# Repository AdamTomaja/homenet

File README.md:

# Home-Net
What is Home-Net? Home-Net is a project which will make Your Home Smart :) 
With Home-Net You can script Your devices in JavaScript and Control them from WEB.

# Screenshots
## Home-Net: Main Page

## Home-Net: Control Panel

# Configuring system and running UMU
## Network Configuration
MQTT Broker has to be configured with static IP.
To do this, please reconfigure Your /etc/dhcpcd.conf file as follows:

```bash
interface wlan0
static ip_address 192.168.0.10/24
static routers=192.168.0.1
static domain_name_servers=127.0.0.1 8.8.8.8 8.8.4.4
```

## TimeZone Configuration
Please remember to set Your timezone on Linux where UMU is installed. 
This is important because You can use time in Javascript flows. 
For example hour is used to determine if turn lights on when motion is detected.

```bash
sudo dpkg-reconfigure tzdata
```

## Start MQTT broker
Please a compatible MQTT broker for the homenet infrastructure. 
I suggest to use Mosquitto. 
You can run install it and run using following command: 

```bash
service mosquitto start
```

## Install Grafana and Influx DB
* Install InfluxDB
```bash
apt-get install influxdb
```

* Check the status of grafana service
```bash
service influxd status
```
You can also open web interface of influxdb: **http://host:8083**

* Install and start the Grafana
```bash
apt-get install grafana
service grafana-server start
```

* Check the status of Grafana **http://host:3000**

## Run UMU server
Execute following command in **homenet-server** directory
```bash
maven spring-boot:run
```

# MQTT Topics
This is description of MQTT topics used by HomeNet UCU and UMU. 

| Topic name          | Description                                                                    | Message class        |
|---------------------|--------------------------------------------------------------------------------|----------------------|
| /ucu/gpio/configure | configure gpio direction, input output pullup                                  | ConfigureGpioMessage |
| /ucu/gpio/set       | set value for gpio on ucu                                                      | SetGpioValueMessage  |
| /umu/gpio/set       | gpio value changed on ucu                                                      | SetGpioValueMessage  |
| /ucu/hello          | request to all ucus to send message to umu with instance names                 | HelloMessage         |
| /umu/hello          | all ucus can introduce themselfs to umu                                        | HelloMessage         |
| /umu/error          | ucu sends to this topic information about errors                               | ErrorMessage         |
| /umu/ping           | ucus sends ping message as answer for ping message from umu                    | PingMessage          |
| /ucu/ping           | umu send ping request to all ucus                                              | PingMessage          |

# UCU Connector
| Signal    | Wire Color    | Connector Pin     |
|-----------|---------------|-------------------|
| 5V        | Red           | 1                 |
| 3.3V      | White         | 2                 |
| IO        | Blue          | 3                 |
| GND       | Black         | 4                 |

# LCU - Light Control Unit - Specification
* One 230V Relay output
* Integrated 5V Power Supply
* External Reset Button - in case of BUGs in software
* External MicroUSB port - for programming
* Fixed to wall like normal light switch - using metal frame from common light switch
* External BLS 2x2 Ports for additional sensors and devices `(GND, 5V, 3.3V, GPIO)`
* Fallback to direct power to light

### NodeMCU Pin Capabilities
| IO Index  | Esp8266 pin   | OUTPUT    | INPUT             | Function          |
|-----------|-------------  |-----------|-------------------|-------------------|
| 0         | Gpio16        | X         | --- (USER Led)    | Notification LED  |
| 1         | Gpio5         | X         | X                 | IO0               |
| 2         | Gpio4         | X         | X                 | IO1               |
| 3         | Gpio0         | X         | X (Flash Button)  | IO2               |   
| 4         | Gpio2         | X         | X                 | IO3               |
| 5         | Gpio14        | X         | X                 | IO4               | 
| 6         | Gpio12        | X         | X                 | IO5               |
| 7         | Gpio13        | X         | X                 | IO6               |
| 8         | Gpio15        | X         | X/2 BOOT,NOPULLUP | Relay             |
| 11 - SD2  | Gpio9         | X         | X                 | Button A          |
| 12 - SD3  | Gpio10        | X         | X                 | Button B          |
| A0        | ADC0          | ---       | ---               | IO8               |

# UMU Configuration
```json
{
  "mqtt": {
    "host": "rpi-umu",
    "port": 1883
  },
  "instances": [
    {
      "id": "ucu-389469",
      "name": "Daily Room",
      "description": "Room I live in",
      "gpios": [
        {
          "name": "Button",
          "mode": "INPUT",
          "isPullup": true,
          "pin": 3,
          "invert": true
        },
        {
          "name": "Led",
          "mode": "OUTPUT",
          "isPullup": false,
          "pin": 4,
          "initialValue": 1,
          "invert": true
        }
      ]
    }
  ]
}
```

## HomeLets
Homelets are small Javascript application which are used to add some logic to Your home behavior. 
The api is very is simple and similar to Arduino. You have setup method and loop. 
It`s possible to add listeners for given control unit and gpio. Also it``s possible last known value of gpio or set new value of output. 

This is example homelet, responsible for turning  on the light when motion is detected or turning off when no  motion detected for 15 minutes.

```javascript
/** Consts **/
var adamsRoom = "Adam Room";
var lightRelay = "Light Relay";
var motionSensor = "Motion Sensor";

var LIGHTS_OFF_TIMEOUT = 15 * 60;

/* Global Variables */
var lastMovementTime = 0;

/* Methods */
function getTimestamp() {
    return new Date().getTime();
}

function getHours() {
    return new Date().getHours();
}

setup = function() {
    this.addListener(adamsRoom, motionSensor, function(value) {
        if(value) {
            var hour = getHours();
            if(hour >= 18 && hour <= 22) {
                this.setValue(adamsRoom, lightRelay, 0);
            }
        }
    });
}

loop = function() {

    var motionSensorValue = this.getValue(adamsRoom, motionSensor);
    var currentTimestamp = getTimestamp();

    if(motionSensorValue) {
        lastMovementTime = currentTimestamp;
    }

    var secondsElapsed = (currentTimestamp - lastMovementTime) / 1000;
    if(secondsElapsed > LIGHTS_OFF_TIMEOUT) {
        this.setValue(adamsRoom, lightRelay, 1);
    }
}
```

# UCU Configuration
Every UCU has embedded configuration server service. 

It exposes WIFI Access Point with Http server. AP will be automatically disabled after 60 seconds after boot time.
Name of AP is the same as chipid (instanceId). 

To configure UCU You should connect with UCU with WiFi and send following http request:
## UCU Configuration Http Request
* host: `192.168.4.1`
* port: `80`
* method: `POST`
* path: `/`
* headers:
    * **ssid** - wifi SSID
    * **password** - wifi PASSWORD
    * **mqtt-host** - MQTT Broker Host
    * **mqtt-port** - MQTT Broker Port

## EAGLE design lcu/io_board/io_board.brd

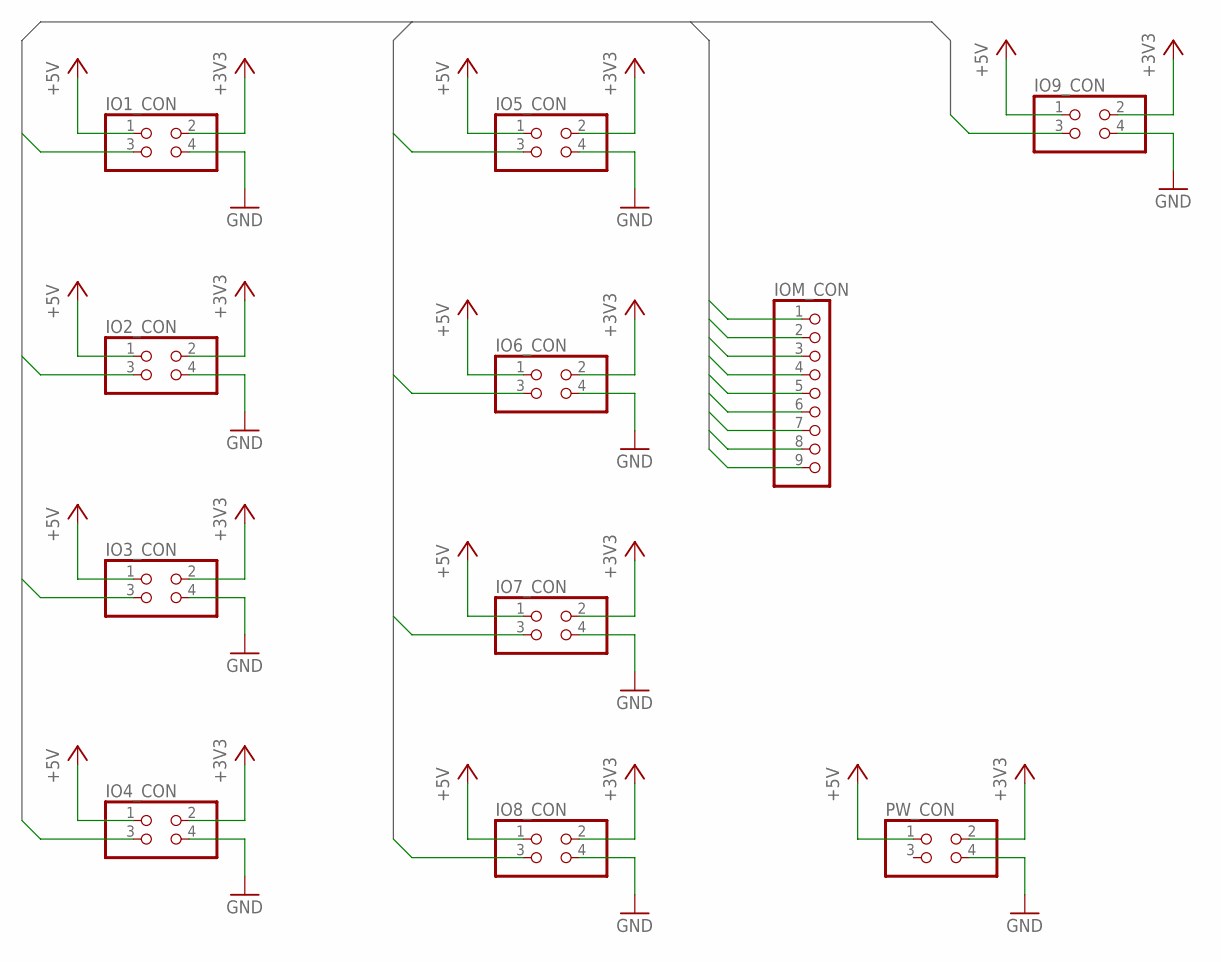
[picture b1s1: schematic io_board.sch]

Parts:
IO1_CON, IO2_CON, IO3_CON, IO4_CON, IO5_CON, IO6_CON, IO7_CON, IO8_CON, IO9_CON: PINHD-2X2; 2X02
IOM_CON: PINHD-1X9; 1X09
PW_CON: PINHD-2X2; 2X02

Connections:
+3V3: IO1_CON.2, IO2_CON.2, IO3_CON.2, IO4_CON.2, IO5_CON.2, IO6_CON.2, IO7_CON.2, IO8_CON.2, IO9_CON.2, PW_CON.2
+5V: IO1_CON.1, IO2_CON.1, IO3_CON.1, IO4_CON.1, IO5_CON.1, IO6_CON.1, IO7_CON.1, IO8_CON.1, IO9_CON.1, PW_CON.1
GND: IO1_CON.4, IO2_CON.4, IO3_CON.4, IO4_CON.4, IO5_CON.4, IO6_CON.4, IO7_CON.4, IO8_CON.4, IO9_CON.4, PW_CON.4
IO0: IO1_CON.3, IOM_CON.1
IO1: IO2_CON.3, IOM_CON.2
IO2: IO3_CON.3, IOM_CON.3
IO3: IO4_CON.3, IOM_CON.4
IO4: IO5_CON.3, IOM_CON.5
IO5: IO6_CON.3, IOM_CON.6
IO6: IO7_CON.3, IOM_CON.7
IO7: IO8_CON.3, IOM_CON.8
IO8: IO9_CON.3, IOM_CON.9

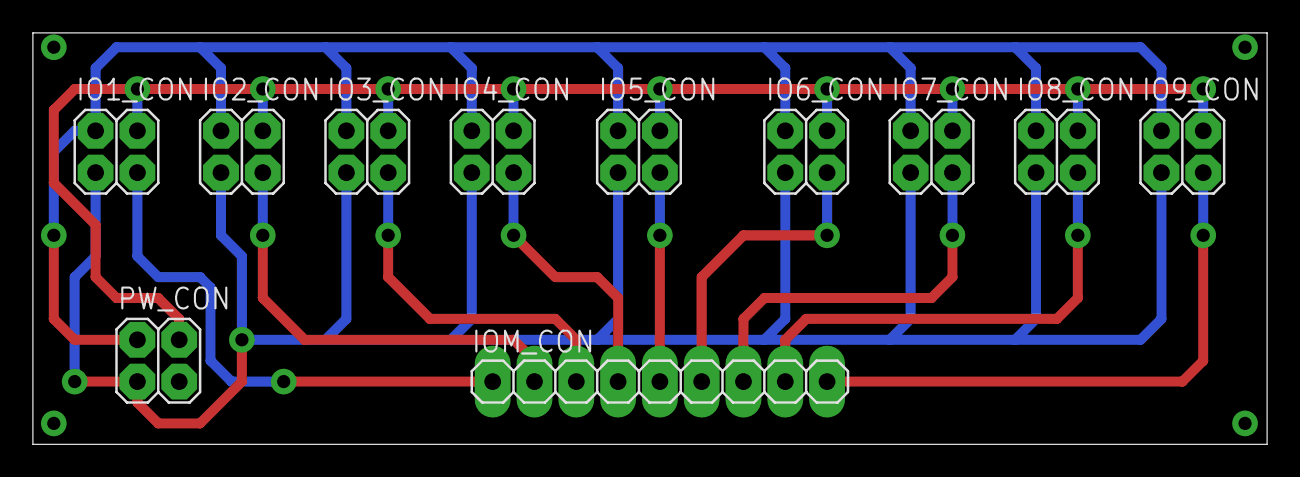
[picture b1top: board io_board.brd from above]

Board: 2 copper layers, 75.0 x 25.0 mm, 11 parts (0 on the bottom side), 12 nets.

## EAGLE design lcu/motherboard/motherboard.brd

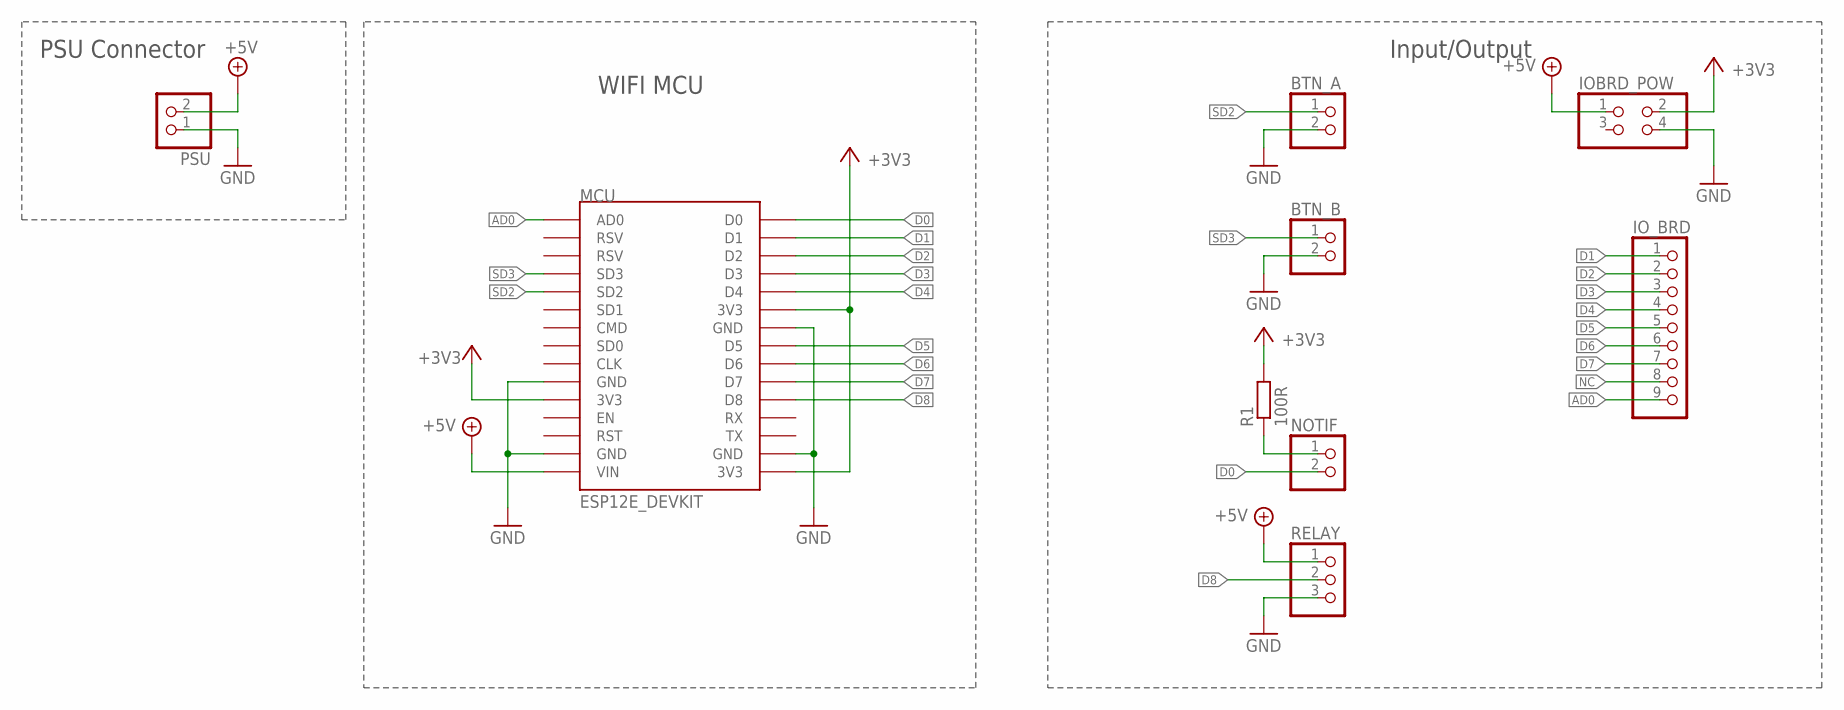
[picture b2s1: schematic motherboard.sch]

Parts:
BTN_A: PINHD-1X2; 1X02
BTN_B: PINHD-1X2; 1X02
IOBRD_POW: PINHD-2X2; 2X02
IO_BRD: PINHD-1X9; 1X09
MCU: ESP12E_DEVKIT
NOTIF: PINHD-1X2; 1X02
PSU: PINHD-1X2; 1X02
R1: 100R; 0204/7
RELAY: PINHD-1X3; 1X03

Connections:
+3V3: IOBRD_POW.2, MCU.3V3@0 (3V3), MCU.3V3@1 (3V3), MCU.3V3@2 (3V3), R1.2
+5V: IOBRD_POW.1, MCU.VIN, PSU.2, RELAY.1
AD0: IO_BRD.9, MCU.AD0
D0: MCU.D0, NOTIF.2
D1: IO_BRD.1, MCU.D1
D2: IO_BRD.2, MCU.D2
D3: IO_BRD.3, MCU.D3
D4: IO_BRD.4, MCU.D4
D5: IO_BRD.5, MCU.D5
D6: IO_BRD.6, MCU.D6
D7: IO_BRD.7, MCU.D7
D8: MCU.D8, RELAY.2
GND: BTN_A.2, BTN_B.2, IOBRD_POW.4, MCU.GND@0 (GND), MCU.GND@1 (GND), MCU.GND@2 (GND), MCU.GND@3 (GND), PSU.1, RELAY.3
unnamed: NOTIF.1, R1.1
NC: IO_BRD.8
SD2: BTN_A.1, MCU.SD2
SD3: BTN_B.1, MCU.SD3

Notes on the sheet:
PSU Connector
Input/Output
WIFI MCU

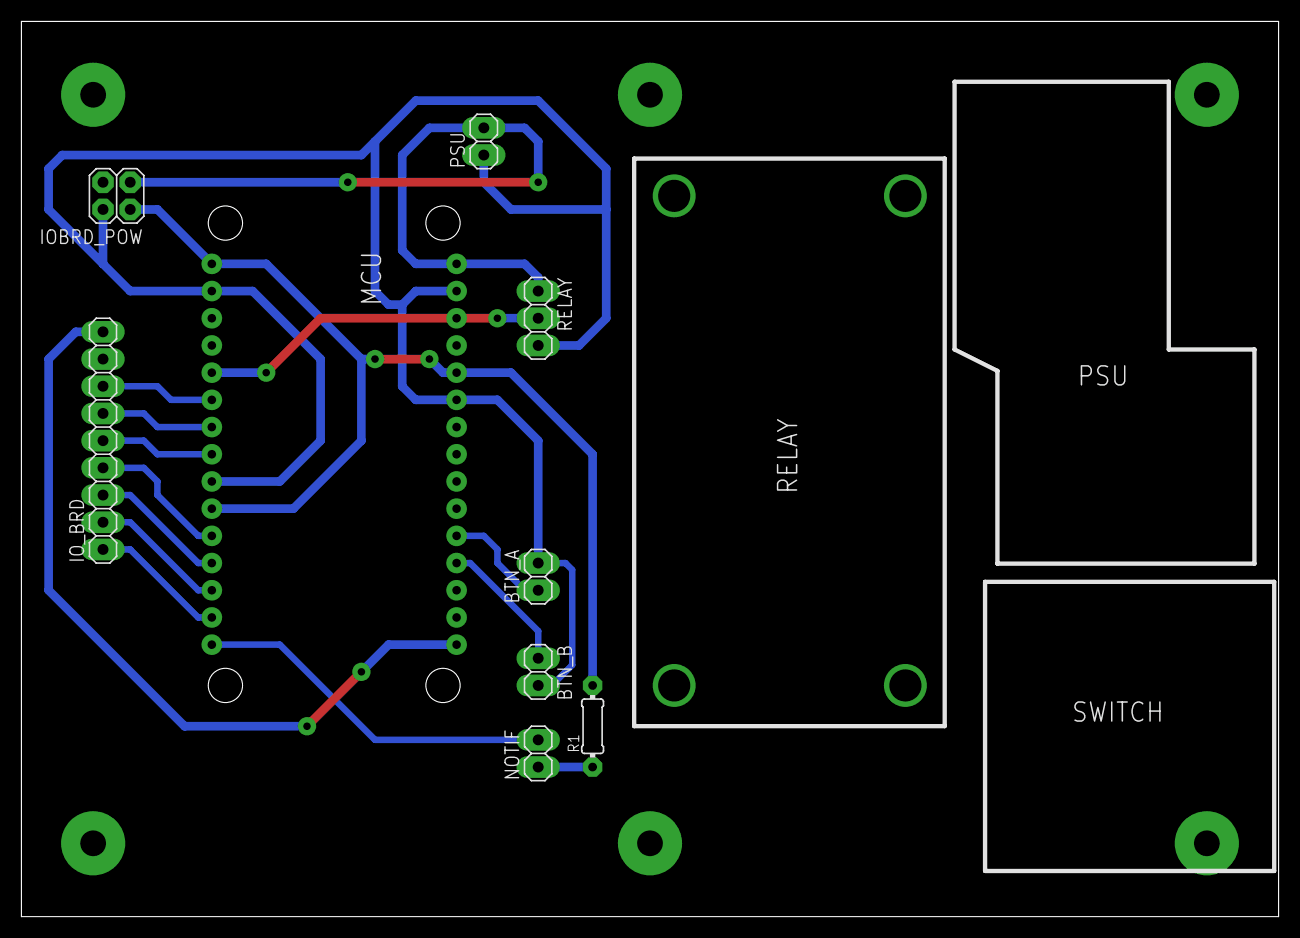
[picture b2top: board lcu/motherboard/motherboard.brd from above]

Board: 2 copper layers, 117.4 x 83.6 mm, 9 parts (0 on the bottom side), 16 nets.

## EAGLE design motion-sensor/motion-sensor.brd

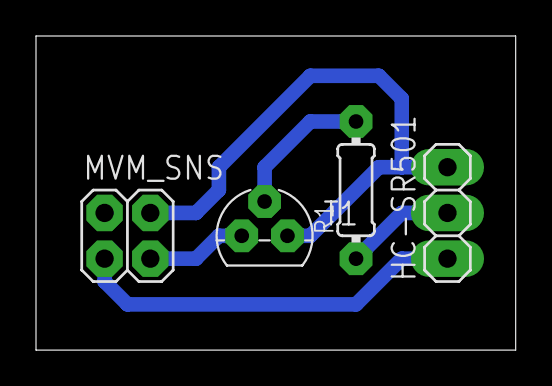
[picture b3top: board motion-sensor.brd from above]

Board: 2 copper layers, 26.6 x 17.4 mm, 4 parts (0 on the bottom side), 5 nets.

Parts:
HC-SR501: 1X03
MVM_SNS: 2X02
R1: 0204/7
T1: BC547; TO92

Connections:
+5V: HC-SR501.1, MVM_SNS.1
GND: HC-SR501.3, MVM_SNS.4, T1.1
unnamed: R1.2, T1.2
unnamed: HC-SR501.2, R1.1
OUTPUT: MVM_SNS.3, T1.3

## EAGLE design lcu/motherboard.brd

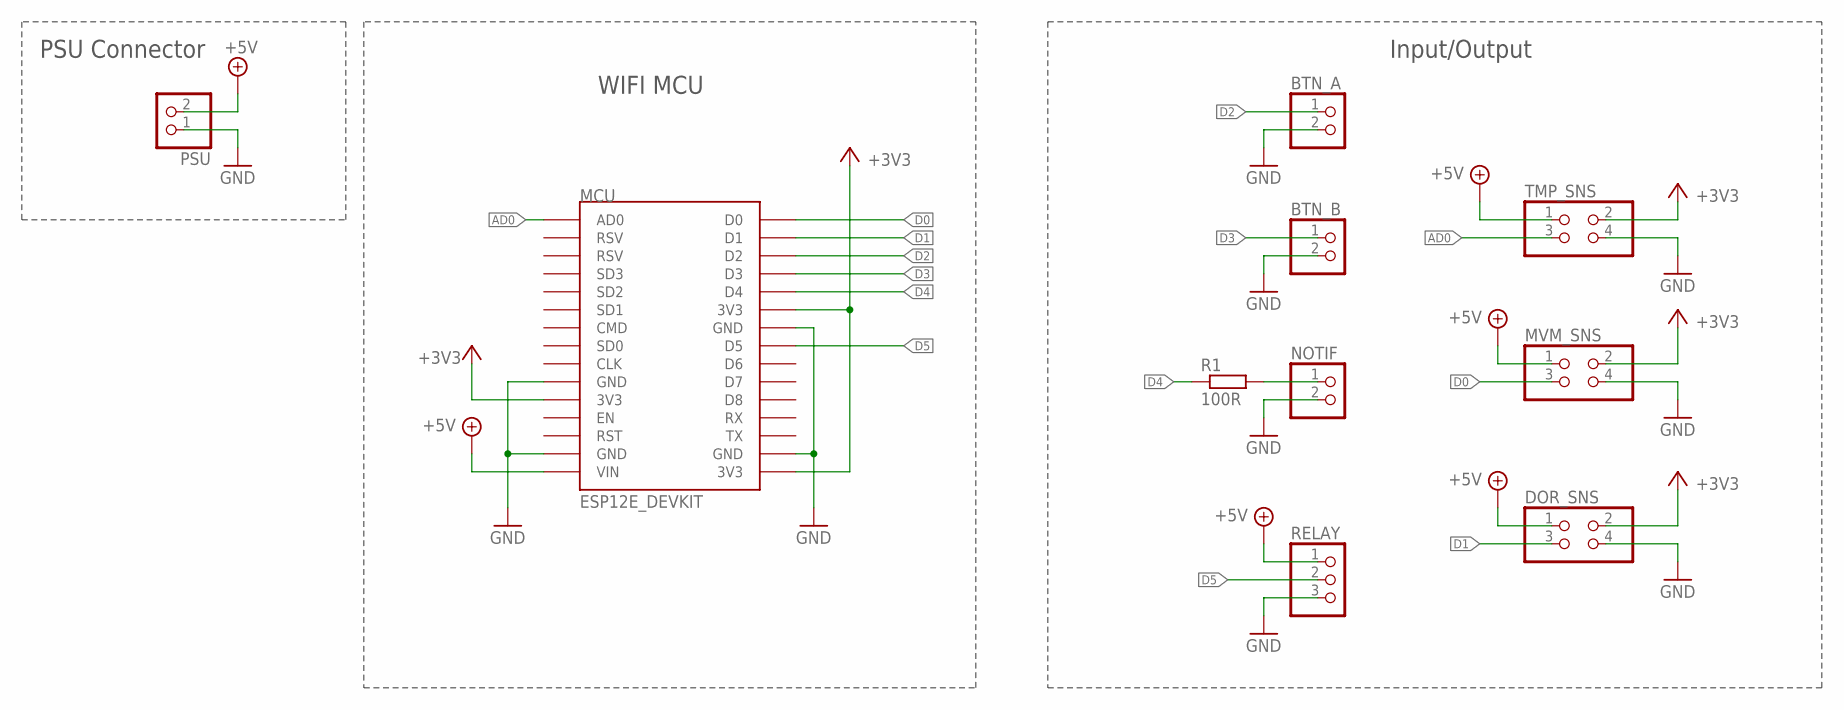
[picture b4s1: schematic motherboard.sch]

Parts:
BTN_A: PINHD-1X2; 1X02
BTN_B: PINHD-1X2; 1X02
DOR_SNS: PINHD-2X2; 2X02
MCU: ESP12E_DEVKIT
MVM_SNS: PINHD-2X2; 2X02
NOTIF: PINHD-1X2; 1X02
PSU: PINHD-1X2; 1X02
R1: 100R; 0204/7
RELAY: PINHD-1X3; 1X03
TMP_SNS: PINHD-2X2; 2X02

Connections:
+3V3: DOR_SNS.2, MCU.3V3@0 (3V3), MCU.3V3@1 (3V3), MCU.3V3@2 (3V3), MVM_SNS.2, TMP_SNS.2
+5V: DOR_SNS.1, MCU.VIN, MVM_SNS.1, PSU.2, RELAY.1, TMP_SNS.1
AD0: MCU.AD0, TMP_SNS.3
D0: MCU.D0, MVM_SNS.3
D1: DOR_SNS.3, MCU.D1
D2: BTN_A.1, MCU.D2
D3: BTN_B.1, MCU.D3
D4: MCU.D4, R1.1
D5: MCU.D5, RELAY.2
GND: BTN_A.2, BTN_B.2, DOR_SNS.4, MCU.GND@0 (GND), MCU.GND@1 (GND), MCU.GND@2 (GND), MCU.GND@3 (GND), MVM_SNS.4, NOTIF.2, PSU.1, RELAY.3, TMP_SNS.4
unnamed: NOTIF.1, R1.2

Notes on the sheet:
PSU Connector
Input/Output
WIFI MCU

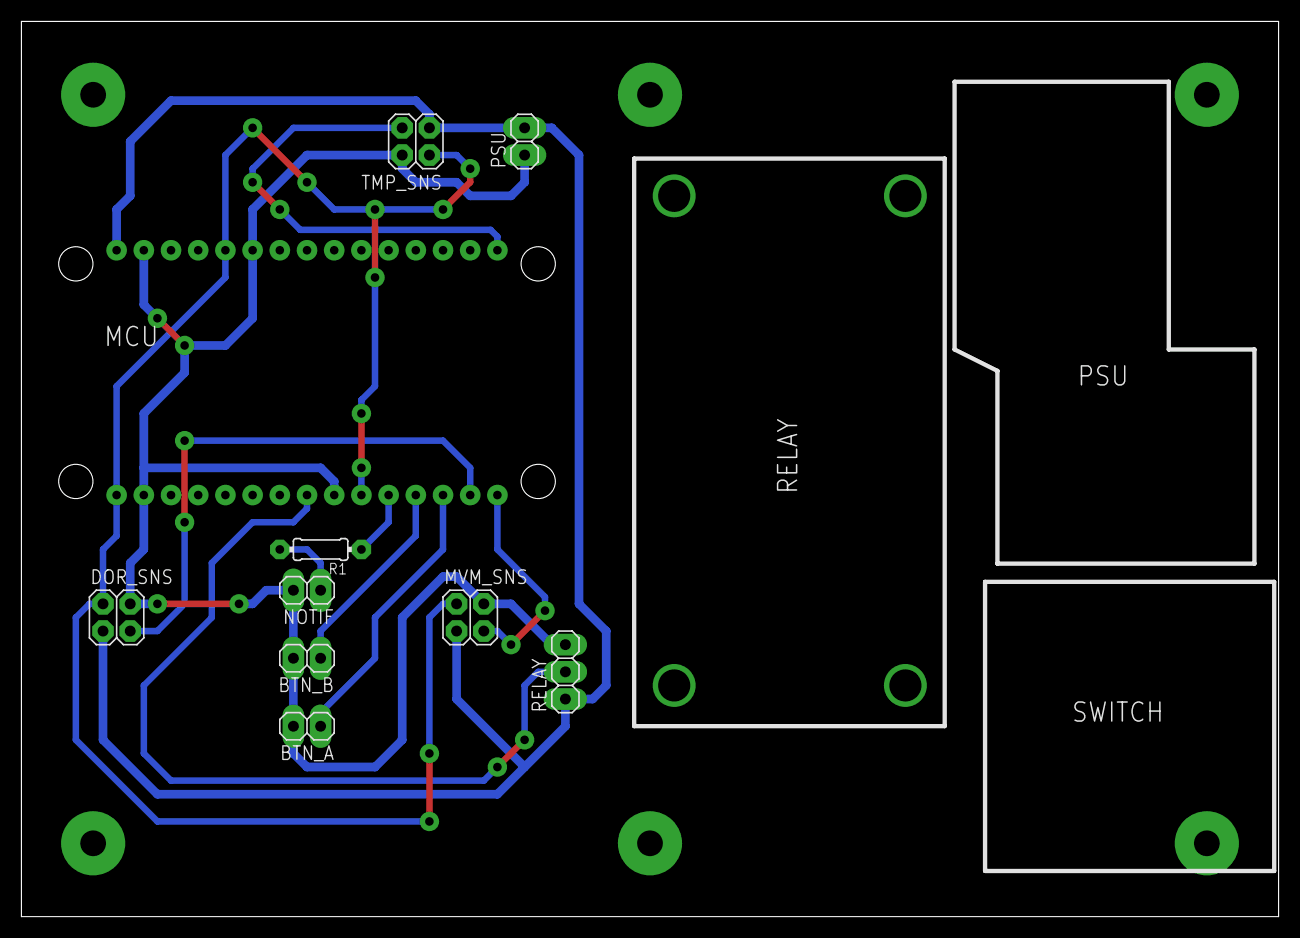
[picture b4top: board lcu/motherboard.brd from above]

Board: 2 copper layers, 117.4 x 83.6 mm, 10 parts (0 on the bottom side), 11 nets.

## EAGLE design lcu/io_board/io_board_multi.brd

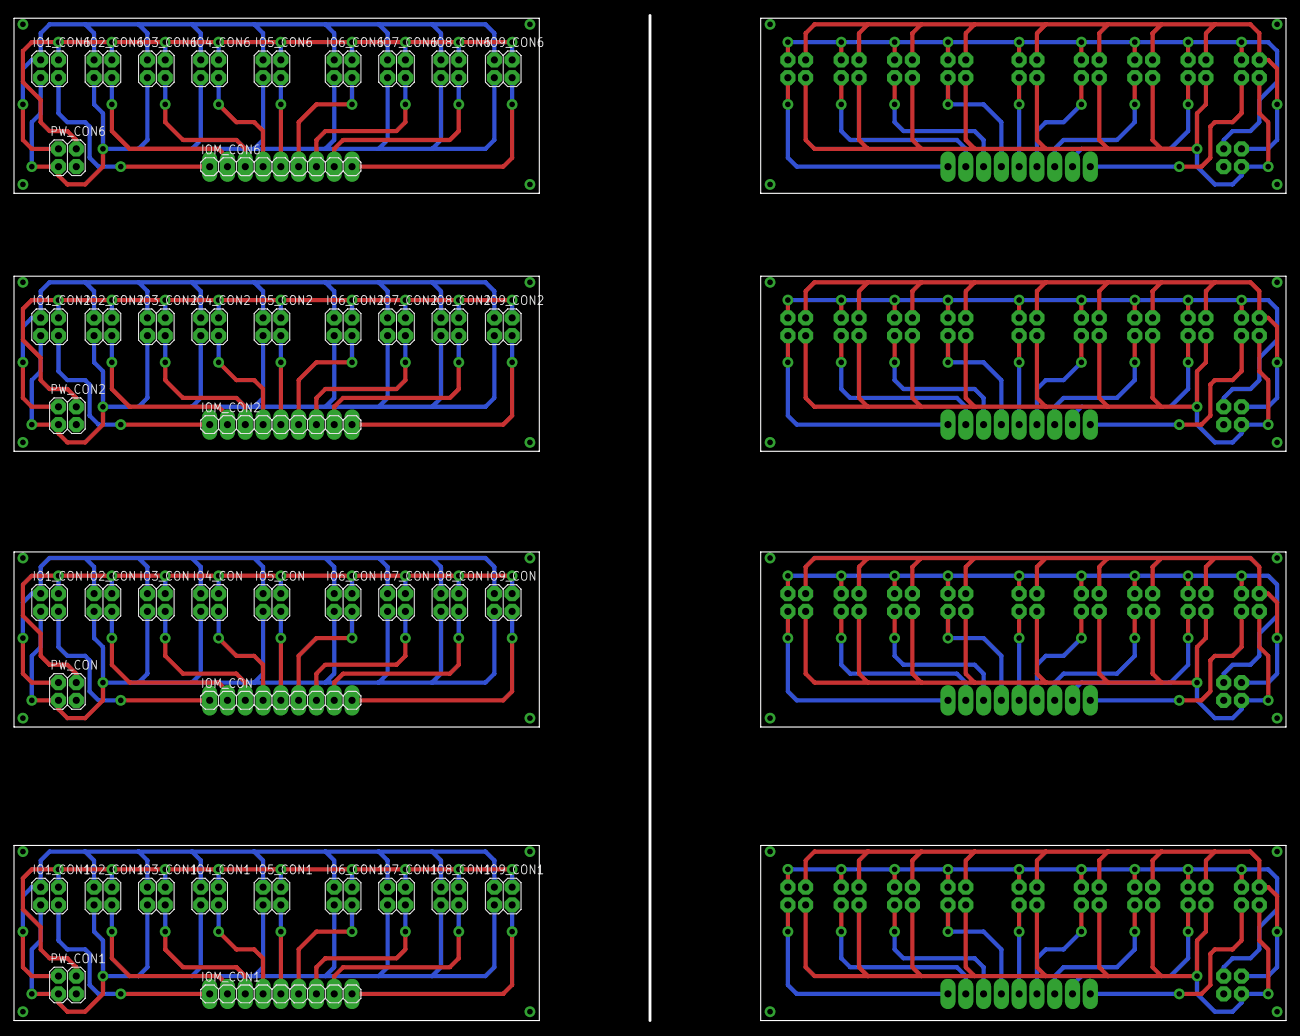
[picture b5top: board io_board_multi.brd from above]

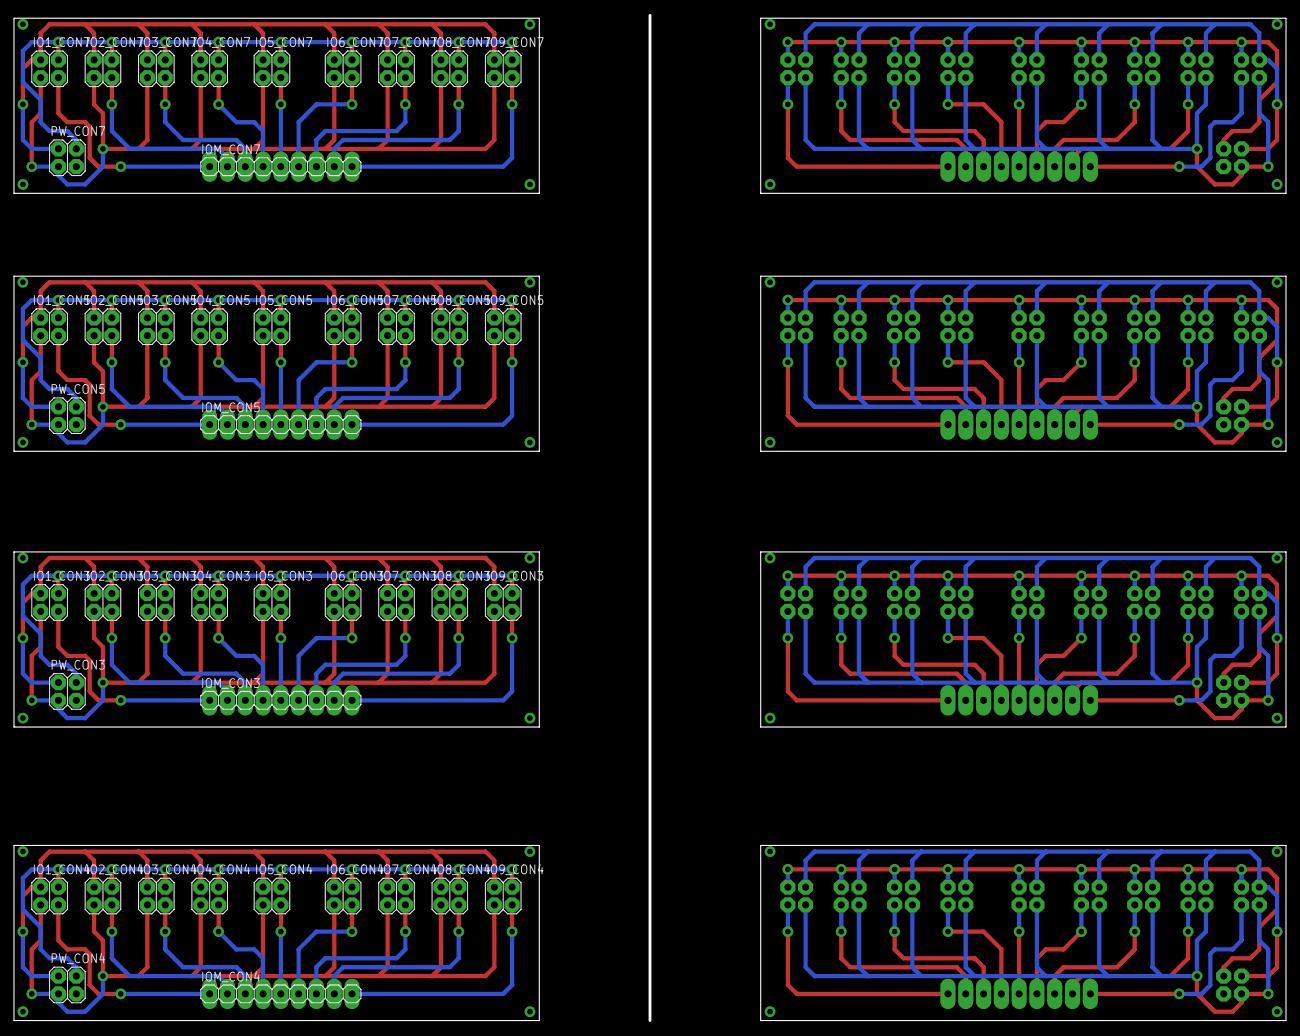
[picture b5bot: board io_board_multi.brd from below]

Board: 2 copper layers, 181.6 x 143.5 mm, 88 parts (44 on the bottom side), 96 nets.

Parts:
IO1_CON, IO1_CON1, IO1_CON2, IO1_CON3, IO1_CON4, IO1_CON5, IO1_CON6, IO1_CON7, IO2_CON, IO2_CON1, IO2_CON2, IO2_CON3, IO2_CON4, IO2_CON5, IO2_CON6, IO2_CON7, IO3_CON, IO3_CON1, IO3_CON2, IO3_CON3, IO3_CON4, IO3_CON5, IO3_CON6, IO3_CON7, IO4_CON, IO4_CON1, IO4_CON2, IO4_CON3, IO4_CON4, IO4_CON5, IO4_CON6, IO4_CON7, IO5_CON, IO5_CON1, IO5_CON2, IO5_CON3, IO5_CON4, IO5_CON5, IO5_CON6, IO5_CON7, IO6_CON, IO6_CON1, IO6_CON2, IO6_CON3, IO6_CON4, IO6_CON5, IO6_CON6, IO6_CON7, IO7_CON, IO7_CON1, IO7_CON2, IO7_CON3, IO7_CON4, IO7_CON5, IO7_CON6, IO7_CON7, IO8_CON, IO8_CON1, IO8_CON2, IO8_CON3, IO8_CON4, IO8_CON5, IO8_CON6, IO8_CON7, IO9_CON, IO9_CON1, IO9_CON2, IO9_CON3, IO9_CON4, IO9_CON5, IO9_CON6, IO9_CON7: 2X02
IOM_CON, IOM_CON1, IOM_CON2, IOM_CON3, IOM_CON4, IOM_CON5, IOM_CON6, IOM_CON7: 1X09
PW_CON, PW_CON1, PW_CON2, PW_CON3, PW_CON4, PW_CON5, PW_CON6, PW_CON7: 2X02

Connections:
+3V1: IO1_CON1.2, IO2_CON1.2, IO3_CON1.2, IO4_CON1.2, IO5_CON1.2, IO6_CON1.2, IO7_CON1.2, IO8_CON1.2, IO9_CON1.2, PW_CON1.2
+3V2: IO1_CON2.2, IO2_CON2.2, IO3_CON2.2, IO4_CON2.2, IO5_CON2.2, IO6_CON2.2, IO7_CON2.2, IO8_CON2.2, IO9_CON2.2, PW_CON2.2
+3V3: IO1_CON.2, IO2_CON.2, IO3_CON.2, IO4_CON.2, IO5_CON.2, IO6_CON.2, IO7_CON.2, IO8_CON.2, IO9_CON.2, PW_CON.2
+3V4: IO1_CON3.2, IO2_CON3.2, IO3_CON3.2, IO4_CON3.2, IO5_CON3.2, IO6_CON3.2, IO7_CON3.2, IO8_CON3.2, IO9_CON3.2, PW_CON3.2
+3V5: IO1_CON4.2, IO2_CON4.2, IO3_CON4.2, IO4_CON4.2, IO5_CON4.2, IO6_CON4.2, IO7_CON4.2, IO8_CON4.2, IO9_CON4.2, PW_CON4.2
+3V6: IO1_CON5.2, IO2_CON5.2, IO3_CON5.2, IO4_CON5.2, IO5_CON5.2, IO6_CON5.2, IO7_CON5.2, IO8_CON5.2, IO9_CON5.2, PW_CON5.2
+3V7: IO1_CON6.2, IO2_CON6.2, IO3_CON6.2, IO4_CON6.2, IO5_CON6.2, IO6_CON6.2, IO7_CON6.2, IO8_CON6.2, IO9_CON6.2, PW_CON6.2
+3V8: IO1_CON7.2, IO2_CON7.2, IO3_CON7.2, IO4_CON7.2, IO5_CON7.2, IO6_CON7.2, IO7_CON7.2, IO8_CON7.2, IO9_CON7.2, PW_CON7.2
+5V: IO1_CON.1, IO2_CON.1, IO3_CON.1, IO4_CON.1, IO5_CON.1, IO6_CON.1, IO7_CON.1, IO8_CON.1, IO9_CON.1, PW_CON.1
+5V1: IO1_CON1.1, IO2_CON1.1, IO3_CON1.1, IO4_CON1.1, IO5_CON1.1, IO6_CON1.1, IO7_CON1.1, IO8_CON1.1, IO9_CON1.1, PW_CON1.1
+5V2: IO1_CON2.1, IO2_CON2.1, IO3_CON2.1, IO4_CON2.1, IO5_CON2.1, IO6_CON2.1, IO7_CON2.1, IO8_CON2.1, IO9_CON2.1, PW_CON2.1
+5V3: IO1_CON3.1, IO2_CON3.1, IO3_CON3.1, IO4_CON3.1, IO5_CON3.1, IO6_CON3.1, IO7_CON3.1, IO8_CON3.1, IO9_CON3.1, PW_CON3.1
+5V4: IO1_CON4.1, IO2_CON4.1, IO3_CON4.1, IO4_CON4.1, IO5_CON4.1, IO6_CON4.1, IO7_CON4.1, IO8_CON4.1, IO9_CON4.1, PW_CON4.1
+5V5: IO1_CON5.1, IO2_CON5.1, IO3_CON5.1, IO4_CON5.1, IO5_CON5.1, IO6_CON5.1, IO7_CON5.1, IO8_CON5.1, IO9_CON5.1, PW_CON5.1
+5V6: IO1_CON6.1, IO2_CON6.1, IO3_CON6.1, IO4_CON6.1, IO5_CON6.1, IO6_CON6.1, IO7_CON6.1, IO8_CON6.1, IO9_CON6.1, PW_CON6.1
+5V7: IO1_CON7.1, IO2_CON7.1, IO3_CON7.1, IO4_CON7.1, IO5_CON7.1, IO6_CON7.1, IO7_CON7.1, IO8_CON7.1, IO9_CON7.1, PW_CON7.1
GND: IO1_CON.4, IO2_CON.4, IO3_CON.4, IO4_CON.4, IO5_CON.4, IO6_CON.4, IO7_CON.4, IO8_CON.4, IO9_CON.4, PW_CON.4
GND1: IO1_CON1.4, IO2_CON1.4, IO3_CON1.4, IO4_CON1.4, IO5_CON1.4, IO6_CON1.4, IO7_CON1.4, IO8_CON1.4, IO9_CON1.4, PW_CON1.4
GND2: IO1_CON2.4, IO2_CON2.4, IO3_CON2.4, IO4_CON2.4, IO5_CON2.4, IO6_CON2.4, IO7_CON2.4, IO8_CON2.4, IO9_CON2.4, PW_CON2.4
GND3: IO1_CON3.4, IO2_CON3.4, IO3_CON3.4, IO4_CON3.4, IO5_CON3.4, IO6_CON3.4, IO7_CON3.4, IO8_CON3.4, IO9_CON3.4, PW_CON3.4
GND4: IO1_CON4.4, IO2_CON4.4, IO3_CON4.4, IO4_CON4.4, IO5_CON4.4, IO6_CON4.4, IO7_CON4.4, IO8_CON4.4, IO9_CON4.4, PW_CON4.4
GND5: IO1_CON5.4, IO2_CON5.4, IO3_CON5.4, IO4_CON5.4, IO5_CON5.4, IO6_CON5.4, IO7_CON5.4, IO8_CON5.4, IO9_CON5.4, PW_CON5.4
GND6: IO1_CON6.4, IO2_CON6.4, IO3_CON6.4, IO4_CON6.4, IO5_CON6.4, IO6_CON6.4, IO7_CON6.4, IO8_CON6.4, IO9_CON6.4, PW_CON6.4
GND7: IO1_CON7.4, IO2_CON7.4, IO3_CON7.4, IO4_CON7.4, IO5_CON7.4, IO6_CON7.4, IO7_CON7.4, IO8_CON7.4, IO9_CON7.4, PW_CON7.4
IO0: IO1_CON.3, IOM_CON.1
IO1: IO2_CON.3, IOM_CON.2
IO2: IO3_CON.3, IOM_CON.3
IO3: IO4_CON.3, IOM_CON.4
IO4: IO5_CON.3, IOM_CON.5
IO5: IO6_CON.3, IOM_CON.6
IO6: IO7_CON.3, IOM_CON.7
IO7: IO8_CON.3, IOM_CON.8
IO8: IO9_CON.3, IOM_CON.9
IO9: IO8_CON1.3, IOM_CON1.8
IO10: IO7_CON1.3, IOM_CON1.7
IO11: IO6_CON1.3, IOM_CON1.6
IO12: IO5_CON1.3, IOM_CON1.5
IO13: IO4_CON1.3, IOM_CON1.4
IO14: IO3_CON1.3, IOM_CON1.3
IO15: IO2_CON1.3, IOM_CON1.2
IO16: IO1_CON1.3, IOM_CON1.1
IO17: IO9_CON1.3, IOM_CON1.9
IO18: IO8_CON2.3, IOM_CON2.8
IO19: IO7_CON2.3, IOM_CON2.7
IO20: IO6_CON2.3, IOM_CON2.6
IO21: IO5_CON2.3, IOM_CON2.5
IO22: IO4_CON2.3, IOM_CON2.4
IO23: IO3_CON2.3, IOM_CON2.3
IO24: IO2_CON2.3, IOM_CON2.2
IO25: IO1_CON2.3, IOM_CON2.1
IO26: IO9_CON2.3, IOM_CON2.9
IO27: IO8_CON3.3, IOM_CON3.8
IO28: IO7_CON3.3, IOM_CON3.7
IO29: IO6_CON3.3, IOM_CON3.6
IO30: IO5_CON3.3, IOM_CON3.5
IO31: IO4_CON3.3, IOM_CON3.4
IO32: IO3_CON3.3, IOM_CON3.3
IO33: IO2_CON3.3, IOM_CON3.2
IO34: IO1_CON3.3, IOM_CON3.1
IO35: IO9_CON3.3, IOM_CON3.9
IO36: IO8_CON4.3, IOM_CON4.8
IO37: IO7_CON4.3, IOM_CON4.7
IO38: IO6_CON4.3, IOM_CON4.6
IO39: IO5_CON4.3, IOM_CON4.5
IO40: IO4_CON4.3, IOM_CON4.4
IO41: IO3_CON4.3, IOM_CON4.3
IO42: IO2_CON4.3, IOM_CON4.2
IO43: IO1_CON4.3, IOM_CON4.1
IO44: IO9_CON4.3, IOM_CON4.9
IO45: IO8_CON5.3, IOM_CON5.8
IO46: IO7_CON5.3, IOM_CON5.7
IO47: IO6_CON5.3, IOM_CON5.6
IO48: IO5_CON5.3, IOM_CON5.5
IO49: IO4_CON5.3, IOM_CON5.4
IO50: IO3_CON5.3, IOM_CON5.3
IO51: IO2_CON5.3, IOM_CON5.2
IO52: IO1_CON5.3, IOM_CON5.1
IO53: IO9_CON5.3, IOM_CON5.9
IO54: IO8_CON6.3, IOM_CON6.8
IO55: IO7_CON6.3, IOM_CON6.7
IO56: IO6_CON6.3, IOM_CON6.6
IO57: IO5_CON6.3, IOM_CON6.5
IO58: IO4_CON6.3, IOM_CON6.4
IO59: IO3_CON6.3, IOM_CON6.3
IO60: IO2_CON6.3, IOM_CON6.2
IO61: IO1_CON6.3, IOM_CON6.1
IO62: IO9_CON6.3, IOM_CON6.9
IO63: IO8_CON7.3, IOM_CON7.8
IO64: IO7_CON7.3, IOM_CON7.7
IO65: IO6_CON7.3, IOM_CON7.6
IO66: IO5_CON7.3, IOM_CON7.5
IO67: IO4_CON7.3, IOM_CON7.4
IO68: IO3_CON7.3, IOM_CON7.3
IO69: IO2_CON7.3, IOM_CON7.2
IO70: IO1_CON7.3, IOM_CON7.1
IO71: IO9_CON7.3, IOM_CON7.9

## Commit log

2017-08-24 Initial LUA connection to wifi script
2017-08-24 Connection over mqtt
2017-08-24 Automatic mqtt reconnection
2017-08-24 Maven project, topics documentation
2017-08-24 Maven project, topics documentation, responding on hello topic
2017-08-24 Configure and set ucu pins
2017-08-24 Spring boot app with mqtt listening and publishing service
2017-08-24 UCU says hello to UMU also after start procedure
2017-08-24 Messaging refactored
2017-08-25 Message handling
2017-08-26 Production environment
2017-08-26 Using node.chipid() as instance id
2017-08-26 Integer conversion
2017-08-26 Page titles and favicon
2017-08-26 Unit id in description
2017-08-26 Settings editor
2017-08-26 Templates refactored
2017-08-26 Different environments configs
2017-08-26 Virtual UCU
2017-08-26 Multithreaded virtual ucu
2017-08-26 Documentation
2017-08-26 Configuration filename logged
2017-08-26 README updated
2017-08-27 WebSocketHandler Unit Test
2017-08-27 WebSocketConfiguration Unit Test
2017-08-27 Message Handling Refactoring
2017-08-27 Initial Hello Message sending moved to application started event listener
2017-08-27 HelloMessageHandler Unit Test
2017-08-27 Logs changed to debug in MessageBus
2017-08-27 Sending new gpio value via websocket
2017-08-27 Inverted type changed to boolean, blocking device buttons until value update not received
2017-08-27 Ugly static converters migrated to spring conversion service
2017-08-27 Messaging packages refactoring
2017-08-27 Static resources packages refactored
2017-08-27 WebSockets packages refactored
2017-08-27 Controllers moved to different packages, refactoring
2017-08-27 Now errors which occured in UCU are displayed in UI
2017-08-27 Screenshots and README
2017-08-27 Spring boot executable packaging
2017-08-27 Start/Stop scripts
2017-08-27 UCU configuration via AP endpoint
2017-08-27 Configuration Server Closing after 60 seconds
2017-08-27 UCU Configuration added to README
2017-08-27 Temperature measuring, adc reading
2017-08-27 Voltage reading
2017-08-28 Value unavailable handling
2017-08-28 WebSocket connection lost alert and hiding the control panels
2017-08-28 GPIO procedures refactored
2017-08-28 Settings analog value from UI
2017-08-28 Ping messages shown in UI
2017-08-30 Started to design schematics
2017-08-30 Casing in eagle
2017-08-30 Pre finished motherboard
2017-08-31 Minor changes in LCU pcb
2017-09-01 Flow for my room
2017-09-02 Motion Sensor Scheme
2017-09-02 Git ignore updated
2017-09-02 Motion Sensor Board
2017-09-02 Motion Sensor Board enhacements
2017-09-02 UCU Connector Pinout Description
2017-09-02 Favorite devices on top of control panel
2017-09-11 Motion sensor added to configuration and flow
2017-09-11 Light timeout increased to 15 minutes
2017-09-11 Timezone info
2017-09-11 MQTT Broker info
2017-09-11 Homelets
2017-09-11 Motion light hour decreased to 21
2017-09-11 Alarm clock homelet
2017-09-12 Homelets gui
2017-09-12 Homelet operations
2017-09-12 Homelets parameters in gui
2017-09-13 New motherboard and IOBoard
2017-09-13 Nodemcu, lcu, pins
2017-09-13 Migrated to lombok
2017-09-13 Homelets called by id
2017-09-14 New homelets configuration gui
2017-09-14 Motion journalist
2018-01-15 RGB W2812 LED Strip
2018-01-18 New units, rgb homelet
2018-01-19 RGB animation and window blinds
2018-01-20 Grafana and influxdb based journaling
2018-03-07 NodeMcu blinds controller
2018-03-20 MQFox
